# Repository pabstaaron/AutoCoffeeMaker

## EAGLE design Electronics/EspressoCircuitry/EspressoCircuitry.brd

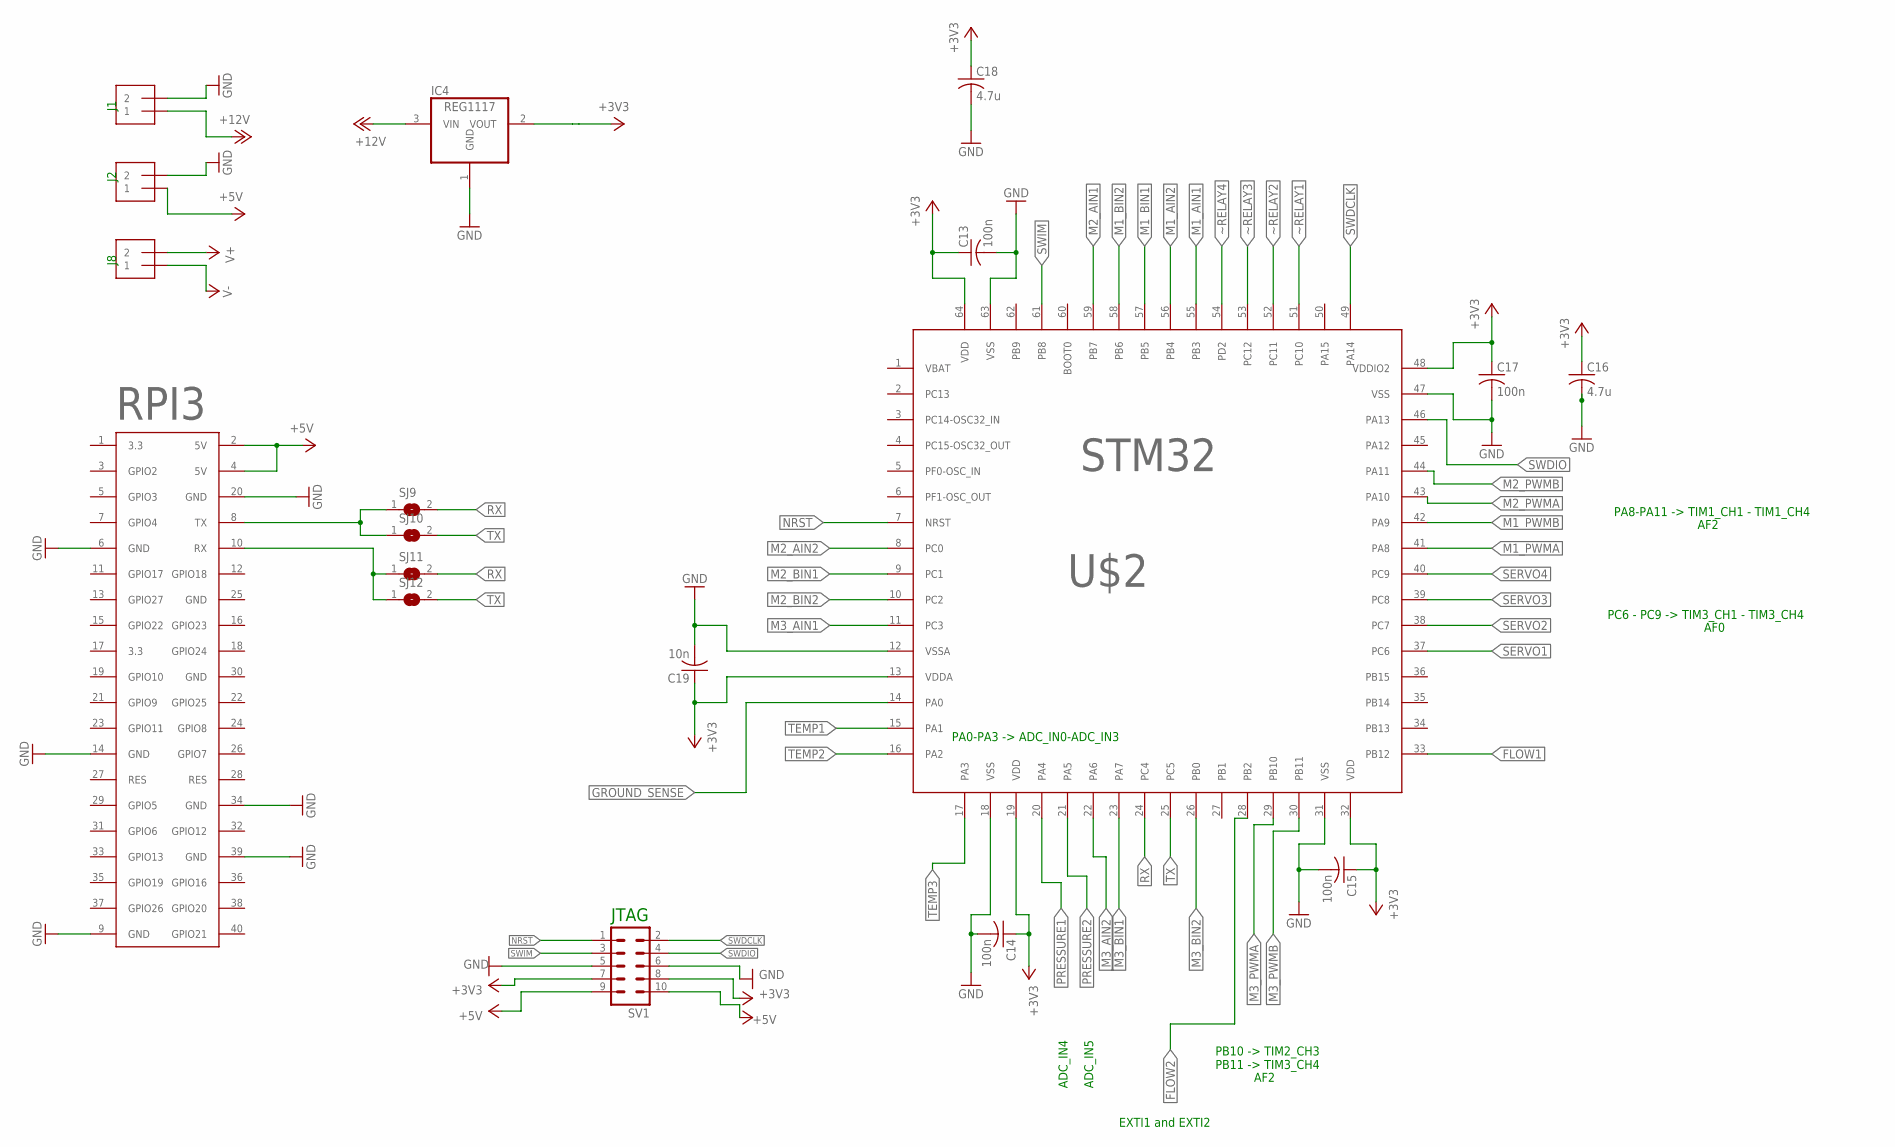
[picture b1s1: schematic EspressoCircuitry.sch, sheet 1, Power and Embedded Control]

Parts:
C13, C14, C15, C17: 100n; C0603
C16, C18: 4.7u; C0603
C19: 10n; C0603
IC4: REG1117; SOT223
J1, J2, J8: 1X2-3.5MM
SJ9, SJ10, SJ11, SJ12: SJ
SV1: MA05-2
U$1: RPI; FE20-2
U$2: STM32F072RBT6LGFP64; PLQFP64-1

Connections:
+3V3: C13.1, C14.1, C15.1, C16.1, C17.1, C18.1, C19.1, IC4.2 (VOUT), SV1.7, SV1.8, U$2.13 (VDDA), U$2.19 (VDD), U$2.32 (VDD), U$2.48 (VDDIO2), U$2.64 (VDD); also elsewhere on the board
+5V: J2.1, SV1.9, SV1.10, U$1.2 (5V), U$1.4 (5V); also elsewhere on the board
+12V: IC4.3 (VIN), J1.1; also elsewhere on the board
FLOW1: U$2.33 (PB12); also elsewhere on the board
FLOW2: U$2.28 (PB2); also elsewhere on the board
GND: C13.2, C14.2, C15.2, C16.2, C17.2, C18.2, C19.2, IC4.1 (GND), J1.2, J2.2, SV1.5, SV1.6, U$1.6 (GND), U$1.9 (GND), U$1.14 (GND), U$1.20 (GND), U$1.34 (GND), U$1.39 (GND), U$2.12 (VSSA), U$2.18 (VSS), U$2.31 (VSS), U$2.47 (VSS), U$2.63 (VSS); also elsewhere on the board
GROUND_SENSE: U$2.14 (PA0); also elsewhere on the board
M1_AIN1: U$2.55 (PB3); also elsewhere on the board
M1_AIN2: U$2.56 (PB4); also elsewhere on the board
M1_BIN1: U$2.57 (PB5); also elsewhere on the board
M1_BIN2: U$2.58 (PB6); also elsewhere on the board
M1_PWMA: U$2.41 (PA8); also elsewhere on the board
M1_PWMB: U$2.42 (PA9); also elsewhere on the board
M2_AIN1: U$2.59 (PB7); also elsewhere on the board
M2_AIN2: U$2.8 (PC0); also elsewhere on the board
M2_BIN1: U$2.9 (PC1); also elsewhere on the board
M2_BIN2: U$2.10 (PC2); also elsewhere on the board
M2_PWMA: U$2.43 (PA10); also elsewhere on the board
M2_PWMB: U$2.44 (PA11); also elsewhere on the board
M3_AIN1: U$2.11 (PC3); also elsewhere on the board
M3_AIN2: U$2.22 (PA6); also elsewhere on the board
M3_BIN1: U$2.23 (PA7); also elsewhere on the board
M3_BIN2: U$2.26 (PB0); also elsewhere on the board
M3_PWMA: U$2.29 (PB10); also elsewhere on the board
M3_PWMB: U$2.30 (PB11); also elsewhere on the board
unnamed: SJ9.1, SJ10.1, U$1.8 (TX)
unnamed: SJ11.1, SJ12.1, U$1.10 (RX)
NRST: SV1.1, U$2.7 (NRST)
PRESSURE1: U$2.20 (PA4); also elsewhere on the board
PRESSURE2: U$2.21 (PA5); also elsewhere on the board
RX: SJ9.2, SJ11.2, U$2.24 (PC4)
SERVO1: U$2.37 (PC6); also elsewhere on the board
SERVO2: U$2.38 (PC7); also elsewhere on the board
SERVO3: U$2.39 (PC8); also elsewhere on the board
SERVO4: U$2.40 (PC9); also elsewhere on the board
SWDCLK: SV1.2, U$2.49 (PA14)
SWDIO: SV1.4, U$2.46 (PA13)
SWIM: SV1.3, U$2.61 (PB8)
TEMP1: U$2.15 (PA1); also elsewhere on the board
TEMP2: U$2.16 (PA2); also elsewhere on the board
TEMP3: U$2.17 (PA3); also elsewhere on the board
TX: SJ10.2, SJ12.2, U$2.25 (PC5)
V+: J8.2; also elsewhere on the board
V-: J8.1; also elsewhere on the board
~RELAY1: U$2.51 (PC10); also elsewhere on the board
~RELAY2: U$2.52 (PC11); also elsewhere on the board
~RELAY3: U$2.53 (PC12); also elsewhere on the board
~RELAY4: U$2.54 (PD2); also elsewhere on the board

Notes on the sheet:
JTAG
PA8-PA11 -> TIM1_CH1 - TIM1_CH4
PC6 - PC9 -> TIM3_CH1 - TIM3_CH4
PB10 -> TIM2_CH3 PB11 -> TIM3_CH4
AF2
AF0
PA0-PA3 -> ADC_IN0-ADC_IN3
ADC_IN4
ADC_IN5
EXTI1 and EXTI2

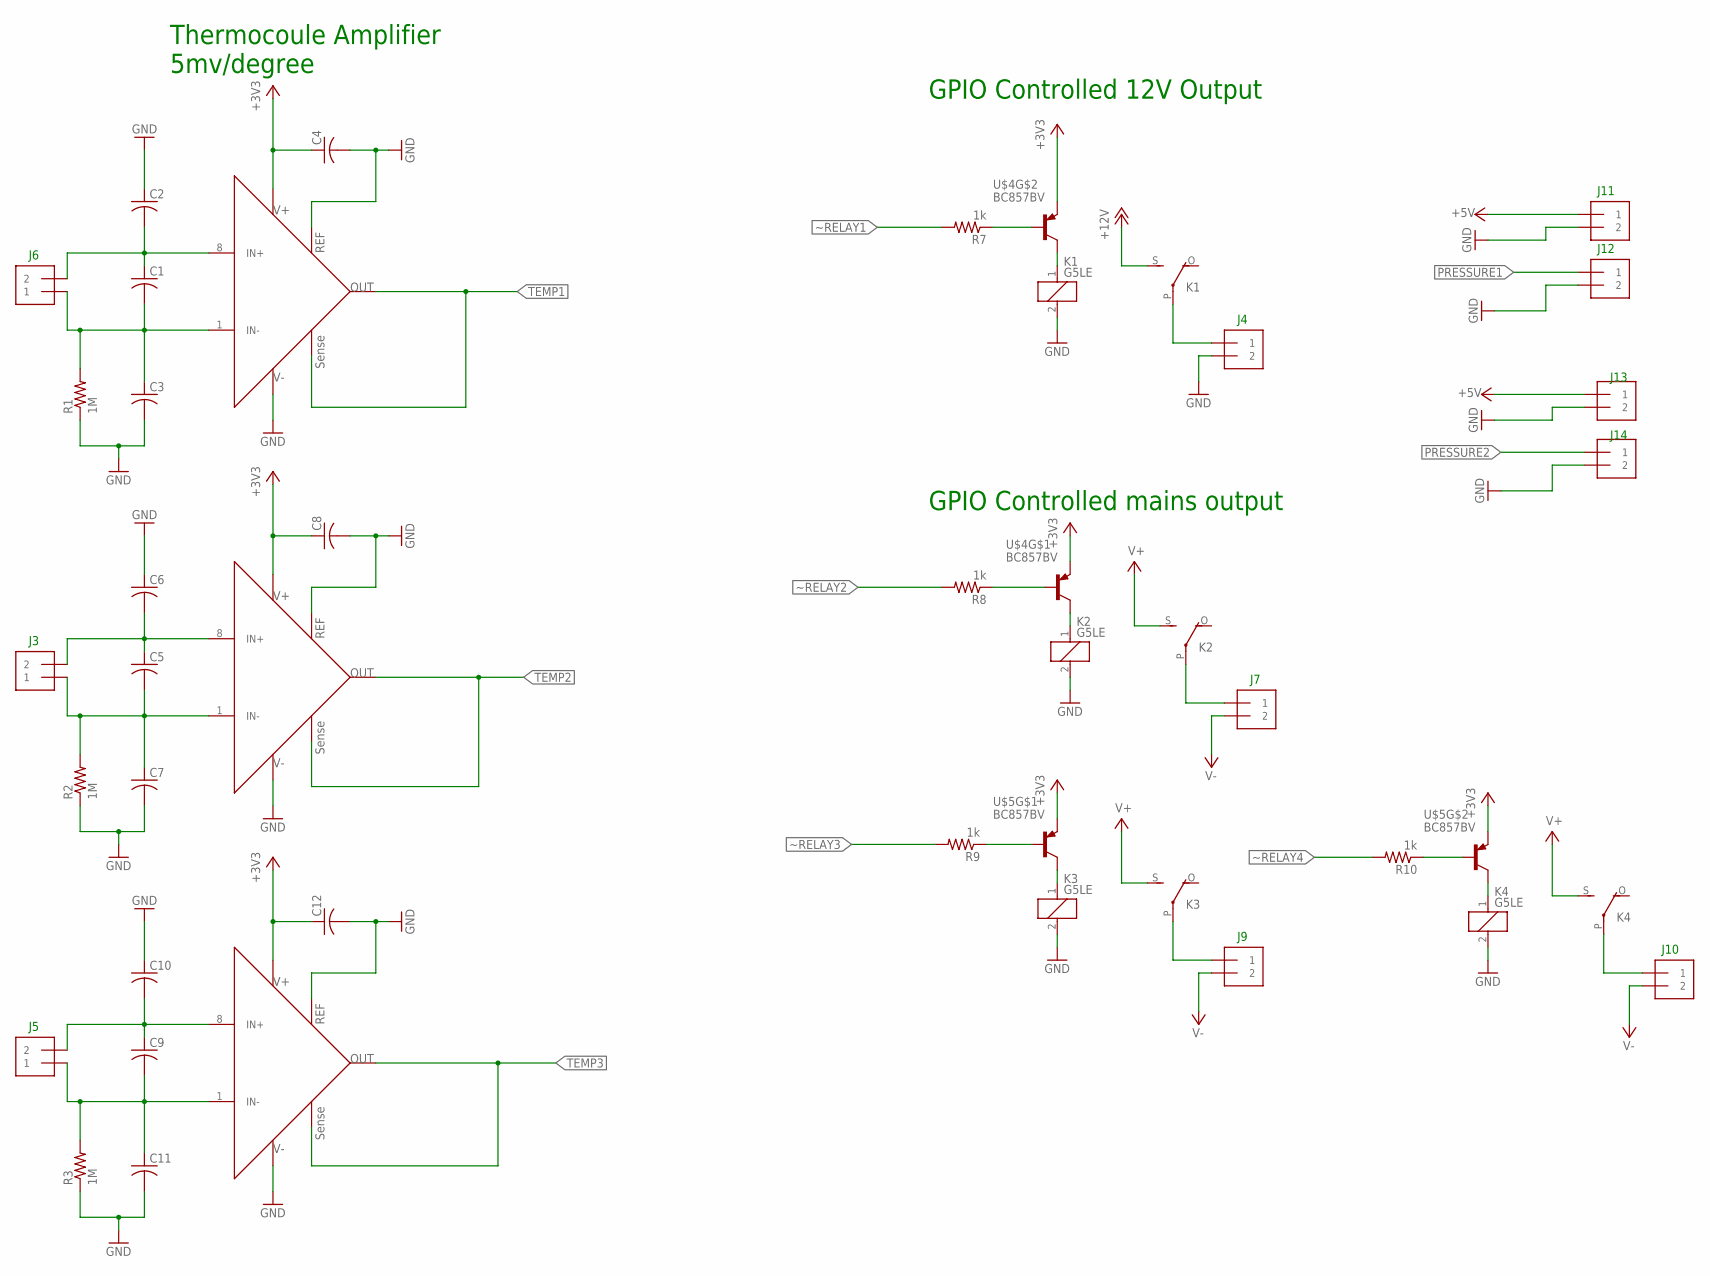
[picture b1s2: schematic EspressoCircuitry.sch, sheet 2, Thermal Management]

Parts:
C1, C2, C3, C4, C5, C6, C7, C8, C9, C10, C11, C12: C-USC0603; C0603
J3, J4, J5, J6, J7, J9, J10, J11, J12, J13, J14: 1X2-3.5MM
K1, K2, K3, K4: G5LE
R1, R2, R3: 1M; R0603
R7, R8, R9, R10: 1k; R0603
U$3, U$6, U$7: AD8494; TSSOP8
U$4, U$5: BC857BV; SOT-563

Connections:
+3V3: C4.1, C8.1, C12.1, U$3.7 (V+), U$4.P$3 (E), U$4.P$6 (E), U$5.P$3 (E), U$5.P$6 (E), U$6.7 (V+), U$7.7 (V+); also elsewhere on the board
+5V: J11.1, J13.1; also elsewhere on the board
+12V: K1.S; also elsewhere on the board
GND: C2.1, C3.2, C4.2, C6.1, C7.2, C8.2, C10.1, C11.2, C12.2, J4.2, J11.2, J12.2, J13.2, J14.2, K1.2, K2.2, K3.2, K4.2, R1.1, R2.1, R3.1, U$3.2 (REF), U$3.3 (V-), U$6.2 (REF), U$6.3 (V-), U$7.2 (REF), U$7.3 (V-); also elsewhere on the board
unnamed: J4.1, K1.P
unnamed: J7.1, K2.P
unnamed: K1.1, U$4.P$1 (C)
unnamed: K2.1, U$4.P$4 (C)
unnamed: C1.1, C2.2, J6.2, U$3.8 (IN+)
unnamed: C1.2, C3.1, J6.1, R1.2, U$3.1 (IN-)
unnamed: J9.1, K3.P
unnamed: K3.1, U$5.P$4 (C)
unnamed: C5.1, C6.2, J3.2, U$6.8 (IN+)
unnamed: C5.2, C7.1, J3.1, R2.2, U$6.1 (IN-)
unnamed: C9.1, C10.2, J5.2, U$7.8 (IN+)
unnamed: C9.2, C11.1, J5.1, R3.2, U$7.1 (IN-)
unnamed: J10.1, K4.P
unnamed: K4.1, U$5.P$1 (C)
unnamed: R7.1, U$4.P$2 (B)
unnamed: R8.1, U$4.P$5 (B)
unnamed: R9.1, U$5.P$5 (B)
unnamed: R10.1, U$5.P$2 (B)
PRESSURE1: J12.1; also elsewhere on the board
PRESSURE2: J14.1; also elsewhere on the board
TEMP1: U$3.5 (SENSE), U$3.6 (OUT); also elsewhere on the board
TEMP2: U$6.5 (SENSE), U$6.6 (OUT); also elsewhere on the board
TEMP3: U$7.5 (SENSE), U$7.6 (OUT); also elsewhere on the board
V+: K2.S, K3.S, K4.S; also elsewhere on the board
V-: J7.2, J9.2, J10.2; also elsewhere on the board
~RELAY1: R7.2; also elsewhere on the board
~RELAY2: R8.2; also elsewhere on the board
~RELAY3: R9.2; also elsewhere on the board
~RELAY4: R10.2; also elsewhere on the board

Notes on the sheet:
GPIO Controlled 12V Output
Thermocoule Amplifier 5mv/degree
GPIO Controlled mains output
J10
J11
J12
J13
J14

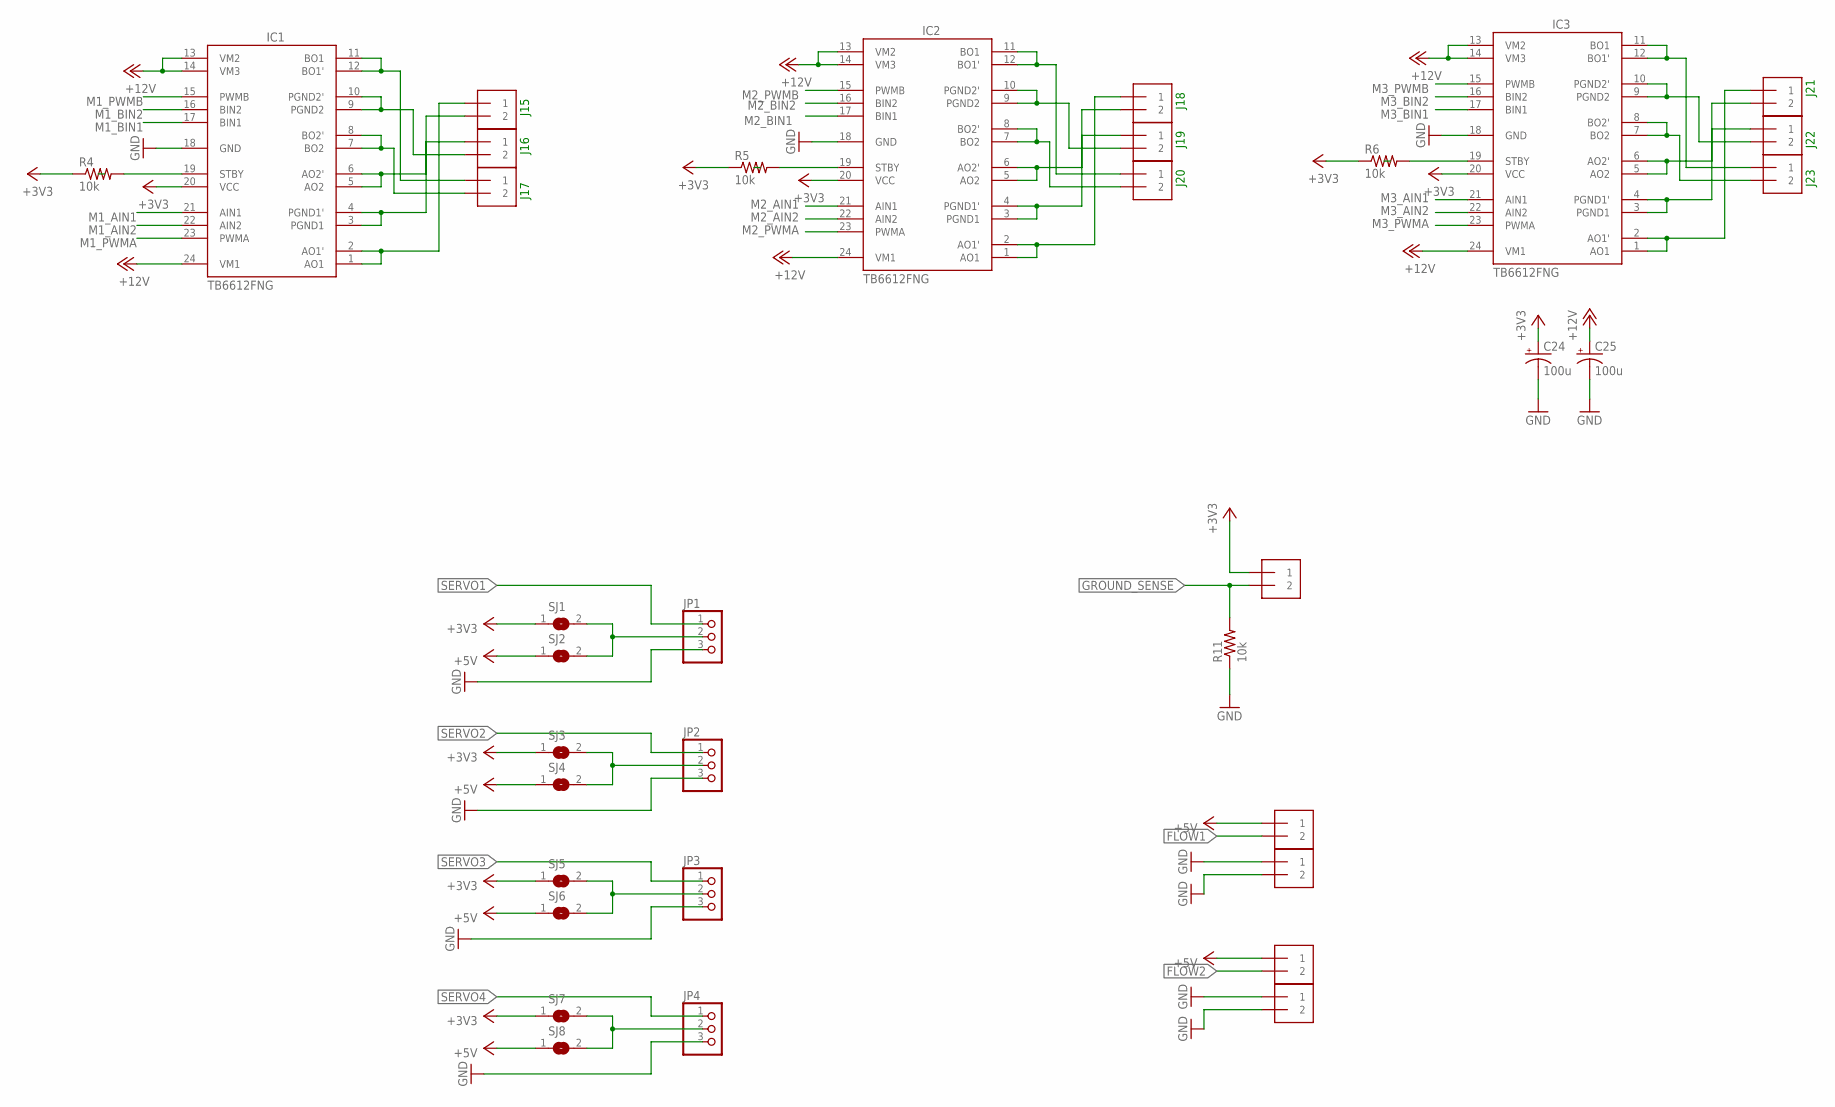
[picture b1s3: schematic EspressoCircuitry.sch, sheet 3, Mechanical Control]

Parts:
C24, C25: 100u; E2,5-5
IC1, IC2, IC3: TB6612FNG; SSOP24
J15, J16, J17, J18, J19, J20, J21, J22, J23, J24, J25, J26, J27, J28: 1X2-3.5MM
JP1, JP2, JP3, JP4: PINHD-1X3; 1X03
R4, R5, R6, R11: 10k; R0603
SJ1, SJ2, SJ3, SJ4, SJ5, SJ6, SJ7, SJ8: SJ

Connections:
+3V3: C24.+, IC1.20 (VCC), IC2.20 (VCC), IC3.20 (VCC), J24.1, R4.1, R5.1, R6.1, SJ1.1, SJ3.1, SJ5.1, SJ7.1; also elsewhere on the board
+5V: J25.1, J27.1, SJ2.1, SJ4.1, SJ6.1, SJ8.1; also elsewhere on the board
+12V: C25.+, IC1.13 (VM2), IC1.14 (VM3), IC1.24 (VM1), IC2.13 (VM2), IC2.14 (VM3), IC2.24 (VM1), IC3.13 (VM2), IC3.14 (VM3), IC3.24 (VM1); also elsewhere on the board
FLOW1: J25.2; also elsewhere on the board
FLOW2: J27.2; also elsewhere on the board
GND: C24.-, C25.-, IC1.18 (GND), IC2.18 (GND), IC3.18 (GND), J26.1, J26.2, J28.1, J28.2, JP1.3, JP2.3, JP3.3, JP4.3, R11.1; also elsewhere on the board
GROUND_SENSE: J24.2, R11.2; also elsewhere on the board
M1_AIN1: IC1.21 (AIN1); also elsewhere on the board
M1_AIN2: IC1.22 (AIN2); also elsewhere on the board
M1_BIN1: IC1.17 (BIN1); also elsewhere on the board
M1_BIN2: IC1.16 (BIN2); also elsewhere on the board
M1_PWMA: IC1.23 (PWMA); also elsewhere on the board
M1_PWMB: IC1.15 (PWMB); also elsewhere on the board
M2_AIN1: IC2.21 (AIN1); also elsewhere on the board
M2_AIN2: IC2.22 (AIN2); also elsewhere on the board
M2_BIN1: IC2.17 (BIN1); also elsewhere on the board
M2_BIN2: IC2.16 (BIN2); also elsewhere on the board
M2_PWMA: IC2.23 (PWMA); also elsewhere on the board
M2_PWMB: IC2.15 (PWMB); also elsewhere on the board
M3_AIN1: IC3.21 (AIN1); also elsewhere on the board
M3_AIN2: IC3.22 (AIN2); also elsewhere on the board
M3_BIN1: IC3.17 (BIN1); also elsewhere on the board
M3_BIN2: IC3.16 (BIN2); also elsewhere on the board
M3_PWMA: IC3.23 (PWMA); also elsewhere on the board
M3_PWMB: IC3.15 (PWMB); also elsewhere on the board
unnamed: IC1.1 (AO1), IC1.2 (AO1'), J15.1
unnamed: IC1.3 (PGND1), IC1.4 (PGND1'), J16.1
unnamed: IC1.5 (AO2), IC1.6 (AO2'), J15.2
unnamed: IC1.7 (BO2), IC1.8 (BO2'), J17.2
unnamed: IC1.9 (PGND2), IC1.10 (PGND2'), J16.2
unnamed: IC1.11 (BO1), IC1.12 (BO1'), J17.1
unnamed: IC1.19 (STBY), R4.2
unnamed: IC2.1 (AO1), IC2.2 (AO1'), J18.1
unnamed: IC2.3 (PGND1), IC2.4 (PGND1'), J19.1
unnamed: IC2.5 (AO2), IC2.6 (AO2'), J18.2
unnamed: IC2.7 (BO2), IC2.8 (BO2'), J20.2
unnamed: IC2.9 (PGND2), IC2.10 (PGND2'), J19.2
unnamed: IC2.11 (BO1), IC2.12 (BO1'), J20.1
unnamed: IC2.19 (STBY), R5.2
unnamed: IC3.1 (AO1), IC3.2 (AO1'), J21.1
unnamed: IC3.3 (PGND1), IC3.4 (PGND1'), J22.1
unnamed: IC3.5 (AO2), IC3.6 (AO2'), J21.2
unnamed: IC3.7 (BO2), IC3.8 (BO2'), J23.2
unnamed: IC3.9 (PGND2), IC3.10 (PGND2'), J22.2
unnamed: IC3.11 (BO1), IC3.12 (BO1'), J23.1
unnamed: IC3.19 (STBY), R6.2
unnamed: JP1.2, SJ1.2, SJ2.2
unnamed: JP2.2, SJ3.2, SJ4.2
unnamed: JP3.2, SJ5.2, SJ6.2
unnamed: JP4.2, SJ7.2, SJ8.2
SERVO1: JP1.1; also elsewhere on the board
SERVO2: JP2.1; also elsewhere on the board
SERVO3: JP3.1; also elsewhere on the board
SERVO4: JP4.1; also elsewhere on the board

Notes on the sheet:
J15
J16
J17
J18
J19
J20
J21
J22
J23

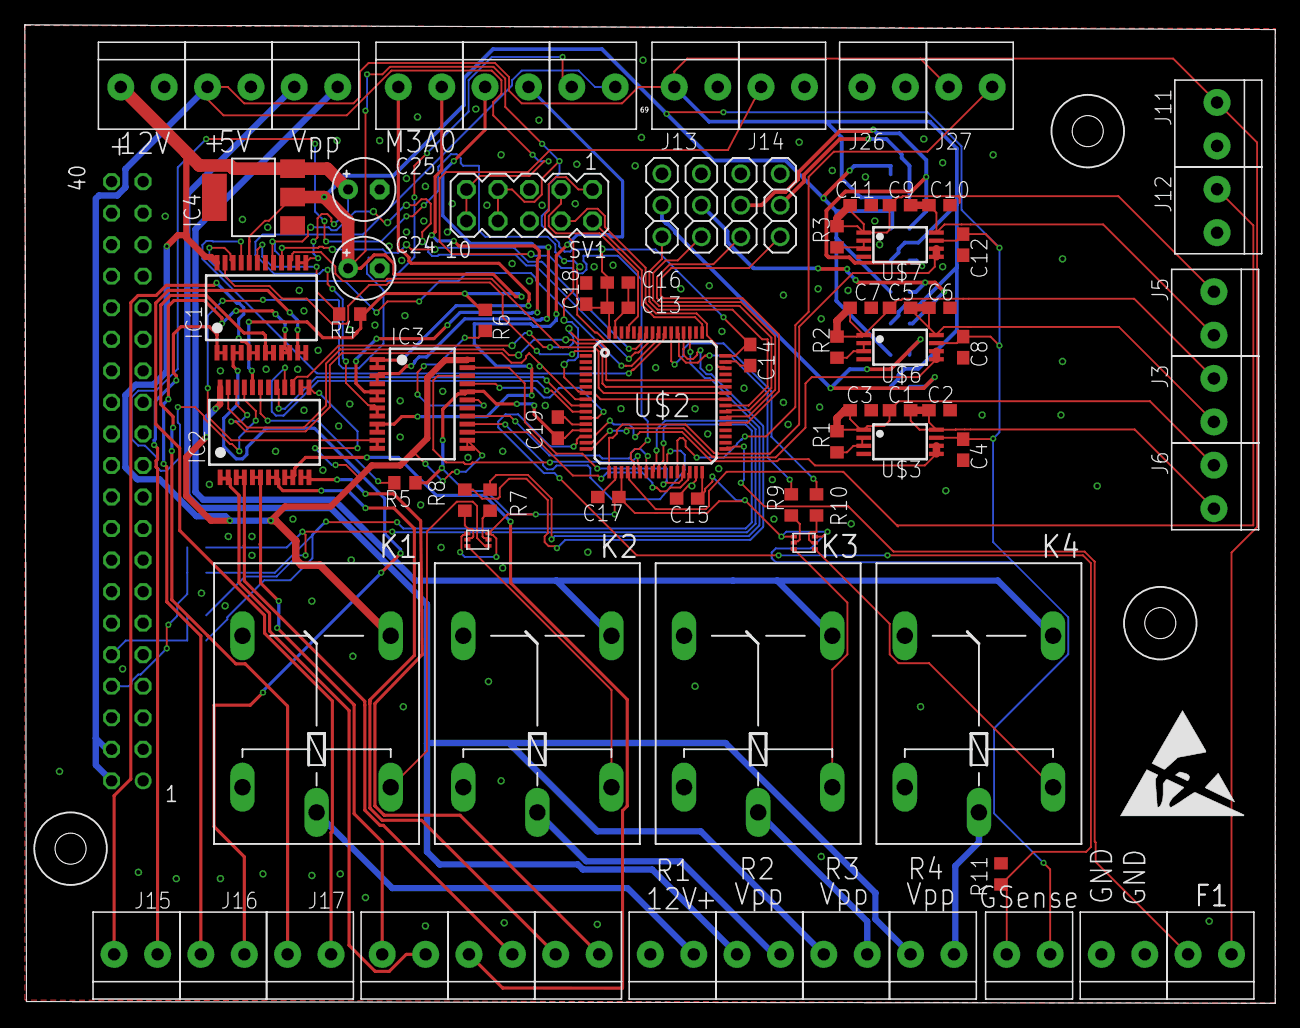
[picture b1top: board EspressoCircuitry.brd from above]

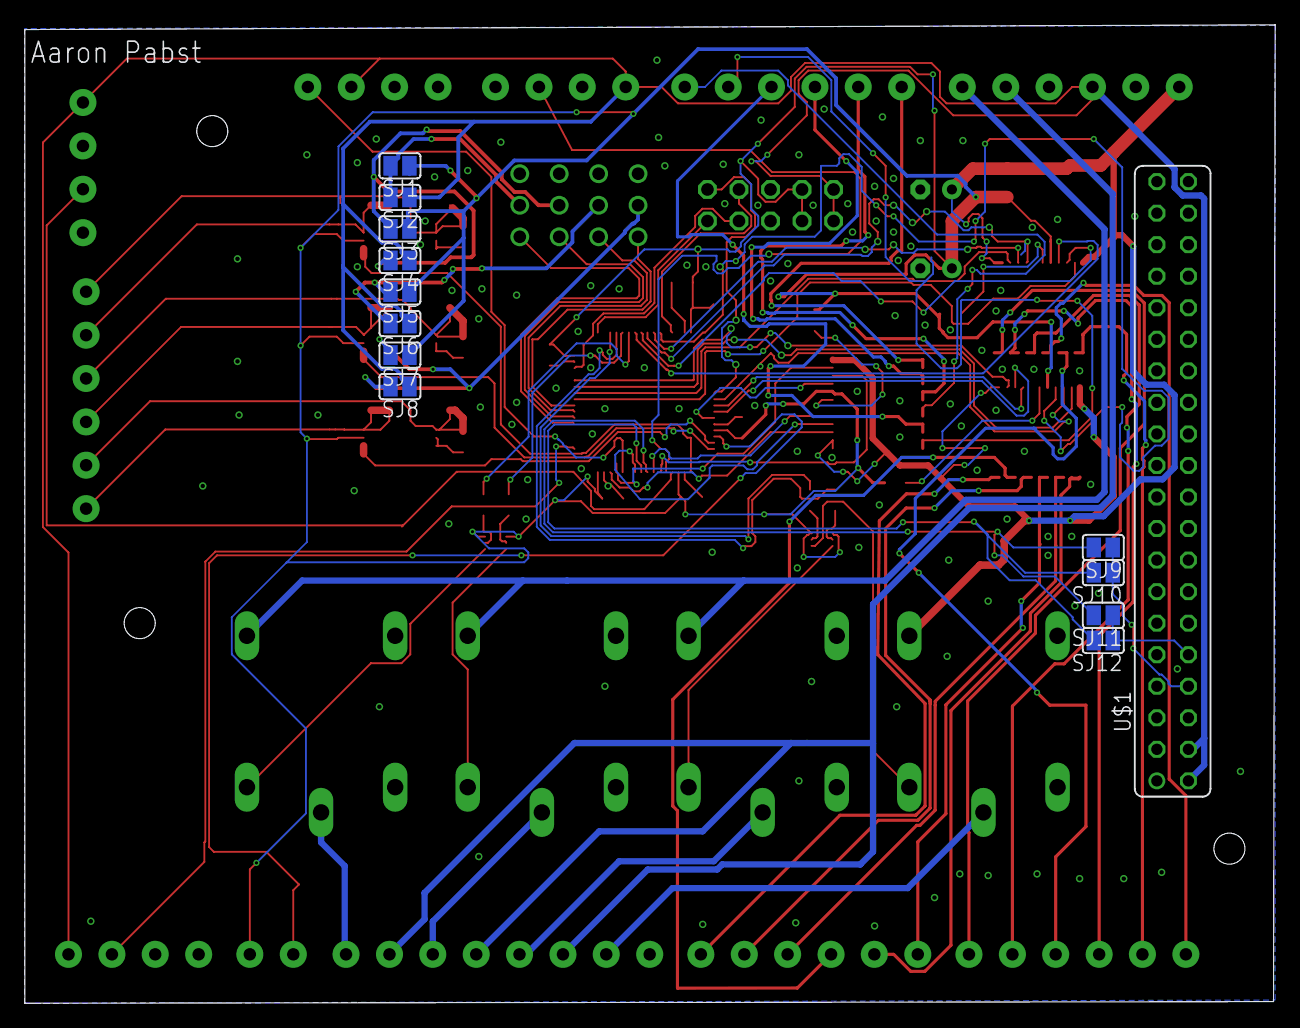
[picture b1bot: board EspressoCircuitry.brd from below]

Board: 2 copper layers, 100.7 x 78.8 mm, 96 parts (12 on the bottom side), 91 nets.

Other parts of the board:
U$8: ESD_10.00
U$9, U$10, U$11: DRIL-2,5

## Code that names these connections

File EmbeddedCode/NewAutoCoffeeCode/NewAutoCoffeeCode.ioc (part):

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Mcu.Name=STM32F072R(8-B)Tx
Mcu.Package=LQFP64
Mcu.UserName=STM32F072RBTx
PA0.Mode=IN0
PA0.Signal=ADC_IN0
PA1.Mode=IN1
PA1.Signal=ADC_IN1
PA10.Signal=S_TIM1_CH3
PA11.Signal=S_TIM1_CH4
PA2.Mode=IN2
PA2.Signal=ADC_IN2
PA3.Mode=IN3
PA3.Signal=ADC_IN3
PA4.Mode=IN4
PA4.Signal=ADC_IN4
PA5.Mode=IN5
PA5.Signal=ADC_IN5
PA6.Signal=GPIO_Output
PA7.Signal=GPIO_Output
PA8.Signal=GPIO_Output
PA9.Signal=GPIO_Output
PB0.Signal=GPIO_Output
PB10.Signal=S_TIM2_CH3
PB11.Signal=S_TIM2_CH4
PB12.Signal=GPXTI12
PB2.Signal=GPXTI2
PB3.Signal=GPIO_Output
PB4.Signal=GPIO_Output
PB5.Signal=GPIO_Output
PB6.Signal=GPIO_Output
PB7.Signal=GPIO_Output
PC0.Signal=GPIO_Output
PC1.Signal=GPIO_Output
PC10.Signal=GPIO_Output
PC11.Signal=GPIO_Output
PC12.Signal=GPIO_Output
PC2.Signal=GPIO_Output
PC3.Signal=GPIO_Output
PC6.Signal=S_TIM3_CH1
PC7.Signal=S_TIM3_CH2
PC8.Signal=S_TIM3_CH3
PC9.Signal=S_TIM3_CH4
PD2.Signal=GPIO_Output
board=custom

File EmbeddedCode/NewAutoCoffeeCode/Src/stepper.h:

#ifndef stepper_H_
#define stepper_H_

#include "stm32f0xx.h"         

#define M1_AIN1 GPIO_PIN_3
#define M1_AIN2 GPIO_PIN_4
#define M1_AIN_BLOCK GPIOB

#define M1_BIN1 GPIO_PIN_5
#define M1_BIN2 GPIO_PIN_6
#define M1_BIN_BLOCK GPIOB

void STEPPER_Init(void);
void rotate(int steps, float speed);
void rotate_degrees(float deg, float speed);

#endif 

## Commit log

2018-02-22 Fixed directory structure
2018-02-22 Set theme jekyll-theme-minimal
2018-02-22 index.html - added minimal example index.html for google pages
2018-02-22 javascript / stylesheets - Added rest of the minimal template
2018-02-22 moved folders around
2018-02-22 TEST- Delete if unnecessary
2018-02-22 Rebase this!
2018-02-23 docs/index.html - Edited templates to represent project
2018-02-23 Setup LaTex Project
2018-02-27 Added bibliograpy
2018-02-27 Created starting introduction
2018-02-27 Added a subsection on how espresso machines work
2018-02-27 Completed draft of introduction
2018-03-02 biblio.bib - Added flask and mock references document.text - Talked about Flask Testing Approach, Project Demonstration, and made a running comment list for Project Tasks
2018-03-03 SeniorProjectProposal: Added small area of "Is it based on other things?" and also moved section at end of "Project Overview" to "Introduction". Also left notes and other stubs so we can talk later.
2018-03-06 Added project overview
2018-03-07 Updated index.html log Document.tex added flask overview, list for project tasks, list for materials
2018-03-07 SeniorProjectProposal: Added mobile UI sections to Overview, Tasks, Materials, Testing, and Demonstration
2018-03-07 SeniorProjectProposal- Added sections for mobile UI to all document after project overview
2018-03-07 I dont know why it made me commit this...
2018-03-07 Got rid of comment
2018-03-07 Fixing line spacing
2018-03-08 Added task breakdown for machine
2018-03-08 Did an editing and proofreading pass
2018-03-08 added small part in flask testing
2018-03-09 Itemized list has to have at least one item for doc to compile.
2018-03-09 Fixed url
2018-03-09 merge
2018-03-09 Fixed many typos and grammatical errors, filled in task list for database/webserver and Data Aggregation and Processing Overview
2018-03-09 Got rid of specific words
2018-03-09 generalized server lanuage to fit different possible choices.
2018-04-05 Made section for Mobile for comm between FLASK, Design/Skeleton
2018-04-05 Senior Project Proposal - Added subsection for pi setup, changed dB info, Added more flushed out version of how the machine would communicate with android
2018-04-06 Started writing skeleton for mobile application, need to know what we aim to control on brewing portion. This will be the most difficult part for sure.
2018-04-11 Added some commentary and beefed up the physical machine overview in the proposal
2018-04-11 document.tex - Added element for Database integration, Project tasks (for flask and DB) and Contigency plan (for flask and DB)
    index.html - added 4/10 meeting
2018-04-12 Added more details for tamping mechanism and flavoring dispenser
2018-04-13 Added some small fixes to my portions for stretch goal clarification.
2018-04-13 Added some preliminary details about the electronics
2018-04-13 Added a figure depicting a thermocouple amplifier
2018-04-14 Added some more info and a tiny little idea for title screen
2018-04-16 Just need to add some more mockup photos.
2018-04-17 Mobile mockups and more info
2018-04-17 Did a merge
2018-04-18 Added some commentary and added information to the tamping description.
2018-04-20 small fixes
2018-05-01 document.tex - modified elliots old stuff, some spelling mistakes, moved contigency to flask section
2018-05-01 small fix, empty section
2018-05-08 Beanster: Added ThreadManager and WifiRunner Thread. Next I will be adding file writing priveleges and the logic to connect to raspBerry PI
2018-05-09 Finished permissions, writing wifi manager next then will work on UI for first page and wifi selection, as well as file writing for previous wifi connections (still debating)
2018-05-12 flask_server - added basic structure of the flask server.
2018-05-12 flask_server - Added README.md
2018-05-18 Finished wifiRunner, going to make UI for connecting device and then test it with RaspberryPI
2018-05-19 flask/stm32.py - added base serial implmenetation of serial communication to stm32 board
2018-05-19 Working on UI and communication for device connection
2018-05-22 Working on UI and recyclerView for UI on wifi selector screen, afterward will work on CoffeeBrewing screen
2018-05-24 Finished recycler view, now finishing up device selection screen and then will test with PI, afterward we can start working on functions of device and mobile app and PI
2018-05-30 Ready to test, having problems with http URL stuff so i figure testing will resolve the issues. Will work on aesthetics as well. Will start working on controls for machine as we go.
2018-05-31 Got some aesthetics done, will continue to do so and work on data integrity as well until we test PI comm
2018-06-02 UI looking better, needs improvement and need to start figuring out connection with PI, also need data integrity and headers
2018-06-09 P400-Ready for testing PI comm
2018-06-10 Added embedded UART code for STM chips
2018-06-14 Finally found a way to identify PI's on LAN and now i can save them off with passwords and other criteria
2018-06-17 settings.py: changed address of setup.json from relative to absolute. This will break running code
2018-06-20 Added some features to make sure wifi is connected and also added auto finding any pi on LAN
2018-06-22 Ready for whatever now...
2018-06-25 Added symbols and footprints for the RPI 3, STM32 chip, AD8494, etc...
2018-06-26 Minor notification fixes
2018-06-26 Changed response codes for connected
2018-06-27 Added some documentation
2018-06-30 Added meeting dates and logs
2018-07-04 Trying to debug sending json to device
2018-07-07 Added more embedded code
2018-07-13 Just some minor additions, small little data sending example
2018-07-16 small change for receiving data on brew command
2018-07-19 bug fixes
2018-07-23 Completed PCB schematic and initial component placement
2018-08-01 Working on styled sliders and spinners and layout for brew page
2018-08-10 More UI changes, indicator seekbar is gonna be tough if i want to change tick marks
2018-08-14 Starting to add functionality. Lots to dogit status
2018-08-21 Adding seekbar animations and still working on functionality
2018-08-22 Working on Layout still and functionality
2018-08-26 index.html - Added 8-25-18 meeting Added file Senior Project Propsal.pdf
2018-08-26 index.html - fixed dead link
2018-08-27 website/added-monthly-calendar
2018-08-27 website/replaced-table-headers-with-table-data
2018-08-28 Working on functionality of Brew activity still
2018-08-28 Added 8-28 meeting
2018-08-28 flask_server: Added rejection template for bad data
2018-09-04 Functionality where it needs to be, Added sliding animation as well
2018-09-06 Lots of changes for WAP
2018-09-15 More logic changes
2018-09-17 Need to get refresh working
2018-09-18 Going to merge next
2018-09-18 Got rid of comments
2018-09-24 Slide animations
2018-09-25 Using my first fragment, also going to used sharedPrefs for user data. Forgot about that :)
2018-09-27 Added fragment logic for login, also added user deletion option on clear cache
2018-09-30 Added updated PCB files
2018-10-02 update/website
2018-10-03 Added login support for first page, as well as structure for user data, will probably do same for device data so i don't have to use files
2018-10-07 added final project files - Pretty complete UART code - LED Drivers for STM32F0 discovery board
2018-10-09 Adding favorites load/save, will do testing soon
2018-10-11 Bugs....but making progress
2018-10-12 Need to just work on favorites now
2018-10-12 Little thingy
2018-10-14 flask_server: Added python code to communicate with STM board - Added pwm code to test functionality Final Project Code - Adjusted UART such that it will consistently work across command states
2018-10-16 Added favorites to code, will add deletion option and clean up a little, then work on aesthetics
2018-10-20 feature/added-stepper-port-code Added some general stepper motor logic.
    This is displayed on the STM32F0 board using the LEDS for the bipolar
    logic.
    Two methods were added:
    rotate(steps, speed)
    rotate_degrees(deg, speed)
    This needs testing and modification using the real stepper motor.
2018-10-24 Created a new project with all the appropriate peripherals and pins initilized.
2018-10-30 Updated code for stepper
2018-10-30 Ported arduino stepper code
2018-11-01 Just fixing up deletion of favorites
2018-11-03 stepper-motor arduino code Added arduino code for Arduino Feather M0
2018-11-03 Finished user info and made some UI changes
2018-11-03 Small fix
2018-11-07 Added code to control the linear actuator
2018-11-07 Added actuator control code
2018-11-08 Added code for multiple servos and multiple steppers.
    First Demo Code for 11/8/2018
2018-11-11 Added startup code, cleaned up code by partitioning serial logic away from main loop.
    Cleaned up unused code,
    Sped up calibration by setting dispense position ~575 steps away
    (without belt slipping 600 is probably extremely close to the actual
    position)
    Problems found:
    - Brew motor needs to be blocking run
2018-11-13 Seperated logic into individual classes. Added logic for Relays
2018-11-14 Added code for test firing the boiler
2018-11-16 changed stepper code to minimum of 1050. Added demo code to arduino
2018-11-16 changed stm->serialUART.
    Added commands to send to arduino.
    Involved modifying old parsing mechanism for the simple `readline()`
    Added DEMO command.
2018-11-16 Edited obvious parts of proposal to reflect today's project
    Also added group times in index.html
2018-11-17 Added starting code for managing a temp regulated brew cycle
2018-11-17 UI improvements
2018-11-20 Added implementation and evaluation sections. Wrote implementation information for all mechanical and embedded pieced. Started the evaluation section
2018-11-20 Added appendices and Evaluation sections
2018-11-25 Beanster changes for data changes
2018-11-29 Hopefully final push
2018-11-29 documents/index.html Added dates met from 11-11 to 11-28
2018-12-04 Latest Coffee Code
2018-12-04 New flask server code
2018-12-05 Hopefully final, fixed things with multiple devices
2018-12-08 FINAL DEMO CODE
2018-12-08 App for demo
2018-12-08 final website commit
2018-12-14 Added demo-day-eval at the bottom of the report
2018-12-16 Added Discoveries and Pitfalls section.[
2018-12-18 Linked code to git
2018-12-18 Final report editing and proofreading pass
